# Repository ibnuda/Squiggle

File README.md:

# Squiggle Keyboard

It's a keyboard family which based on my circumstances, preferences, and
observed usages.

Requirements:

- 5 columns per hand.
  My right pinky is almost useless.
- At most 3 keys for each side's thumb row.
  My right thumb key is almost useless.
- No numrow.
  It's harder and more cumbersome to use than a numpad on a layer.
- Split.
  Typing on single flat keyboard hurts my arms in a lot of use cases.
- Symmetric.
  Personal preferences.

This family keyboard repo will not have any of the following features:

- OLED Screen: useless.
- LEDs: useless for me and hurt my eyes.
- Rotary Encoder: useless for me.
- Hotswap: I need a commitment.
- Case for `Low Profile`: defeating the whole purpose of ***LOW*** profile.

## Screenshot

### Standard

- MX and Alps style switches.
- 34 Keys.
- 4x2u thumb keys.
- 2 Promicros.
- TRRS/TRS cable.

### Low Profile

- Dongguan Kaihua Electronics Co., Ltd (originally named Longhua Electronics)'s
  Choc style switches.
- 34 Keys.
- 4x2u thumb keys.
- 2 Promicros.
- TRRS/TRS cable.

### 36 Keys

- MX and Alps style switches.
- 36 Keys.
- 4x2u+2x1.25u thumb keys.
- 2 Promicros.
- TRRS/TRS cable.

### Minimalist

- MX and Alps style switches.
- 34 Keys.
- 4x2u thumb keys.
- 1 Promicros.
- "Amphenol 10 wire" cable.

### Goldberg

(Because it's more complex than necessary. It's just a damn keyboard.)

- MX and Alps style switches.
- 34 - 38 Keys.
- 4x2u or 8x1u thumb keys. (or anything in between)
- 2 Promicros.
- TRRS/TRS cable.

## Confirmed Working PCBs

### Standard

Example firmware: [QMK's master branch](https://github.com/qmk/qmk_firmware/tree/master/keyboards/squiggle/keymaps/rick)

### Goldberg

Example firmware: [QMK's master branch](https://github.com/qmk/qmk_firmware/tree/master/keyboards/squiggle/keymaps/rick-complicated)

### Low Profile

Example firmware: [QMK's master branch](https://github.com/qmk/qmk_firmware/tree/master/keyboards/squiggle/keymaps/rick)

### Minimalist

Example firmware: [Ibnuda's fork](https://github.com/ibnuda/qmk_firmware/tree/squiggle-minimalist/keyboards/squiggle_minimalist/keymaps/rick)

## Disclaimer

I haven't printed some of it. But, theoretically, they should just work.
Oh, if things go wrong, I won't take any responisibilities.

## Additional Note

Any files with `mokou_*.kicad_mod` in `libs/footprints` are made by [Jokan Hiyou](https://twitter.com/jokanhiyou)
and belong to hers.
I just dither them and made them kicad footprints.

## License

GPLv3.

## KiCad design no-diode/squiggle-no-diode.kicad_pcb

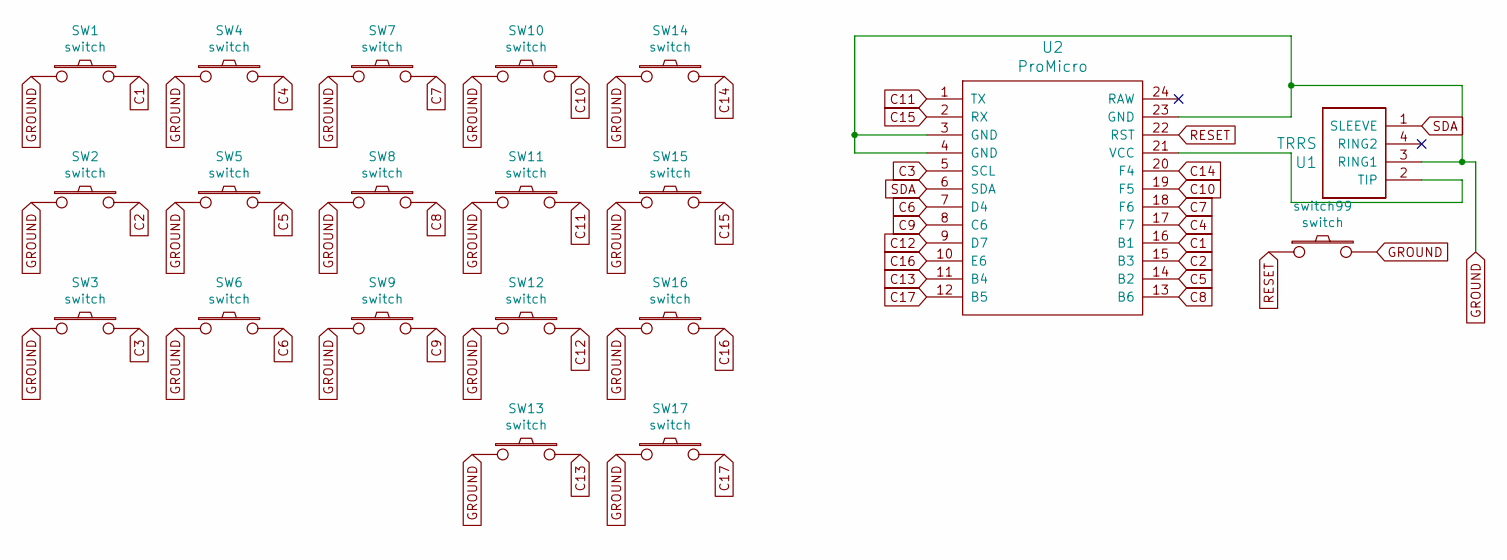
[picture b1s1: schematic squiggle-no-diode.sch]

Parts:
SW1, SW2, SW3, SW4, SW5, SW6, SW7, SW8, SW9, SW10, SW11, SW12, SW14, SW15, SW16: switch; 1u-dual
SW13, SW17: switch; 2u-dual
U1: TRRS; trrs
U2: ProMicro; promicro
switch99: switch; SW_PUSH_6mm_H4.3mm

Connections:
C1: SW1.2, U2.16 (B1)
C2: SW2.2, U2.15 (B3)
C3: SW3.2, U2.5 (SCL)
C4: SW4.2, U2.17 (F7)
C5: SW5.2, U2.14 (B2)
C6: SW6.2, U2.7 (D4)
C7: SW7.2, U2.18 (F6)
C8: SW8.2, U2.13 (B6)
C9: SW9.2, U2.8 (C6)
C10: SW10.2, U2.19 (F5)
C11: SW11.2, U2.1 (TX)
C12: SW12.2, U2.9 (D7)
C13: SW13.2, U2.11 (B4)
C14: SW14.2, U2.20 (F4)
C15: SW15.2, U2.2 (RX)
C16: SW16.2, U2.10 (E6)
C17: SW17.2, U2.12 (B5)
GROUND: SW1.1, SW2.1, SW3.1, SW4.1, SW5.1, SW6.1, SW7.1, SW8.1, SW9.1, SW10.1, SW11.1, SW12.1, SW13.1, SW14.1, SW15.1, SW16.1, SW17.1, U1.3 (RING1), U2.3 (GND), U2.4 (GND), U2.23 (GND), switch99.2
unnamed: U1.2 (TIP), U2.21 (VCC)
RESET: U2.22 (RST), switch99.1
SDA: U1.1 (SLEEVE), U2.6 (SDA)

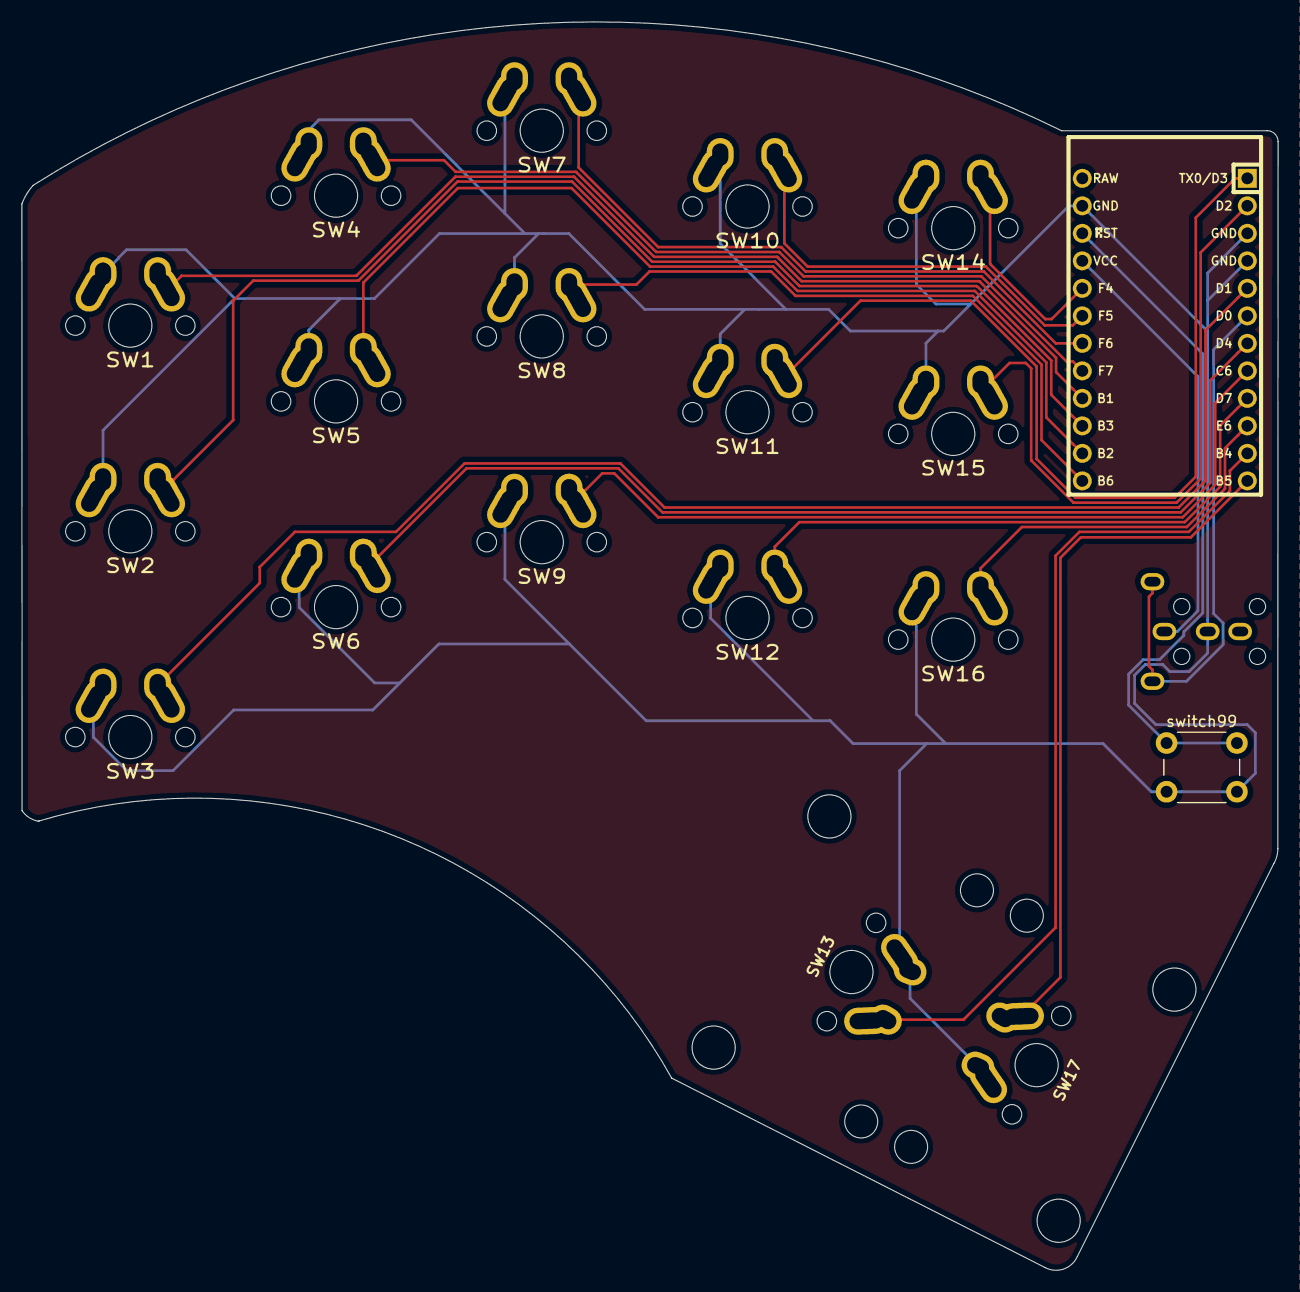
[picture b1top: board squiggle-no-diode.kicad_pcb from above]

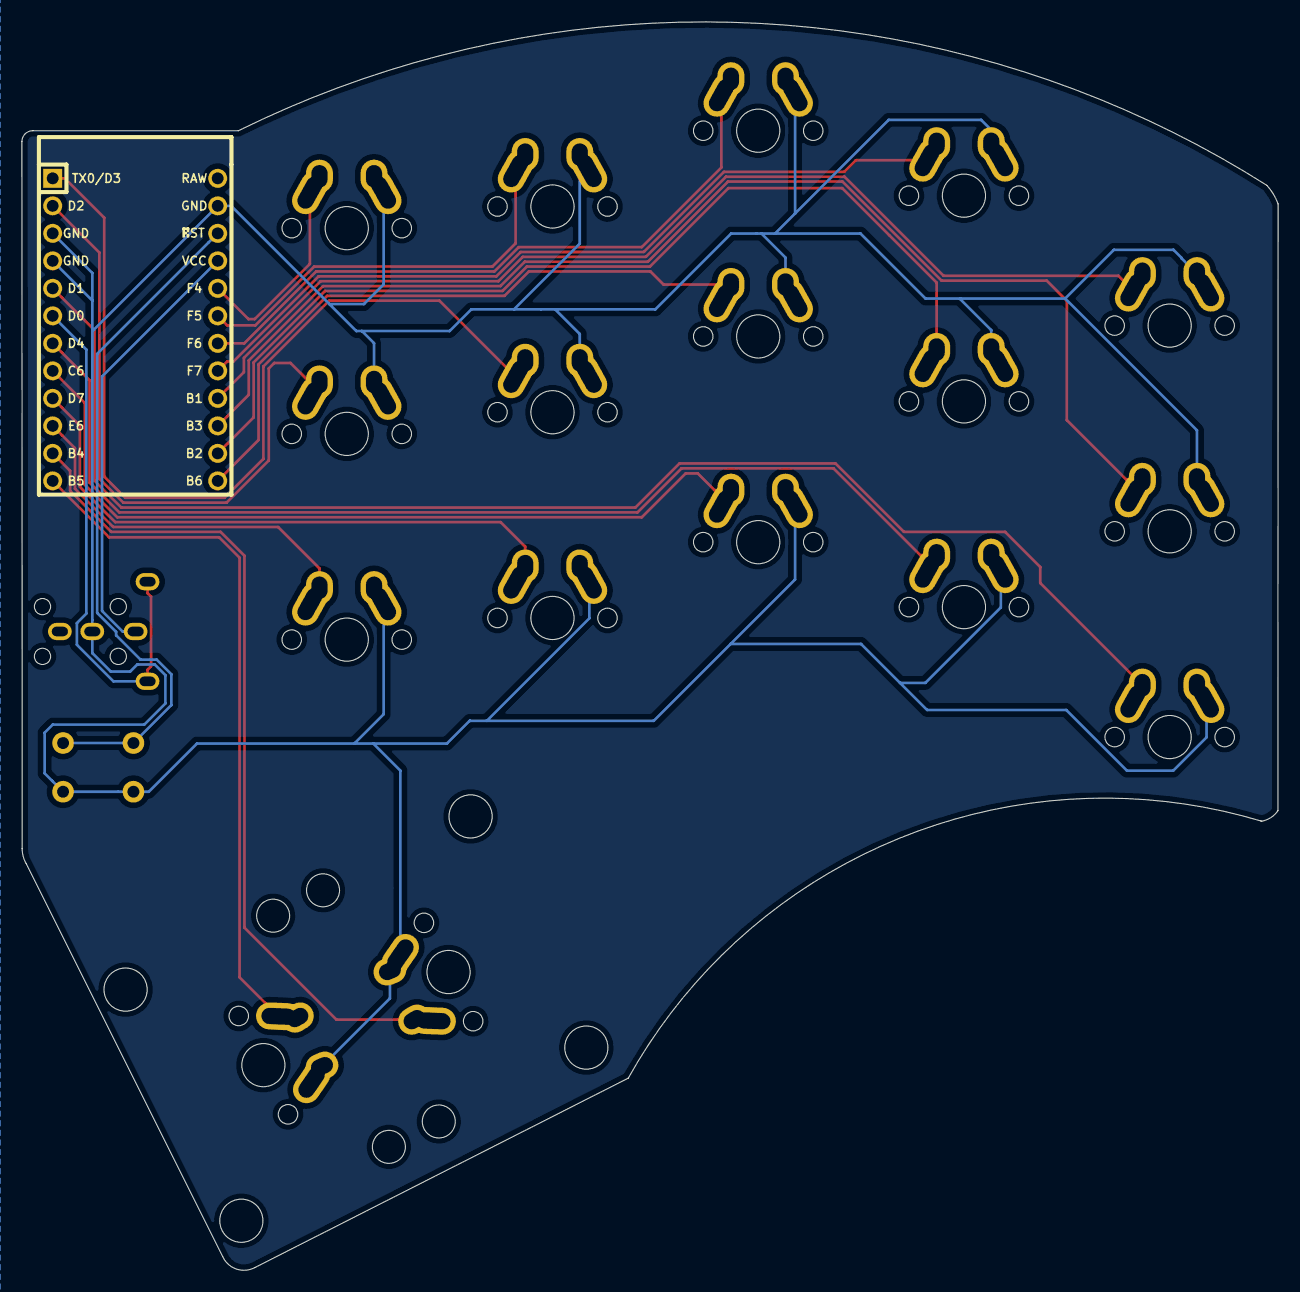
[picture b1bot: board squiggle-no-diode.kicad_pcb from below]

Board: 2 copper layers, 116.0 x 115.3 mm, 20 parts (2 on the bottom side), 21 nets.

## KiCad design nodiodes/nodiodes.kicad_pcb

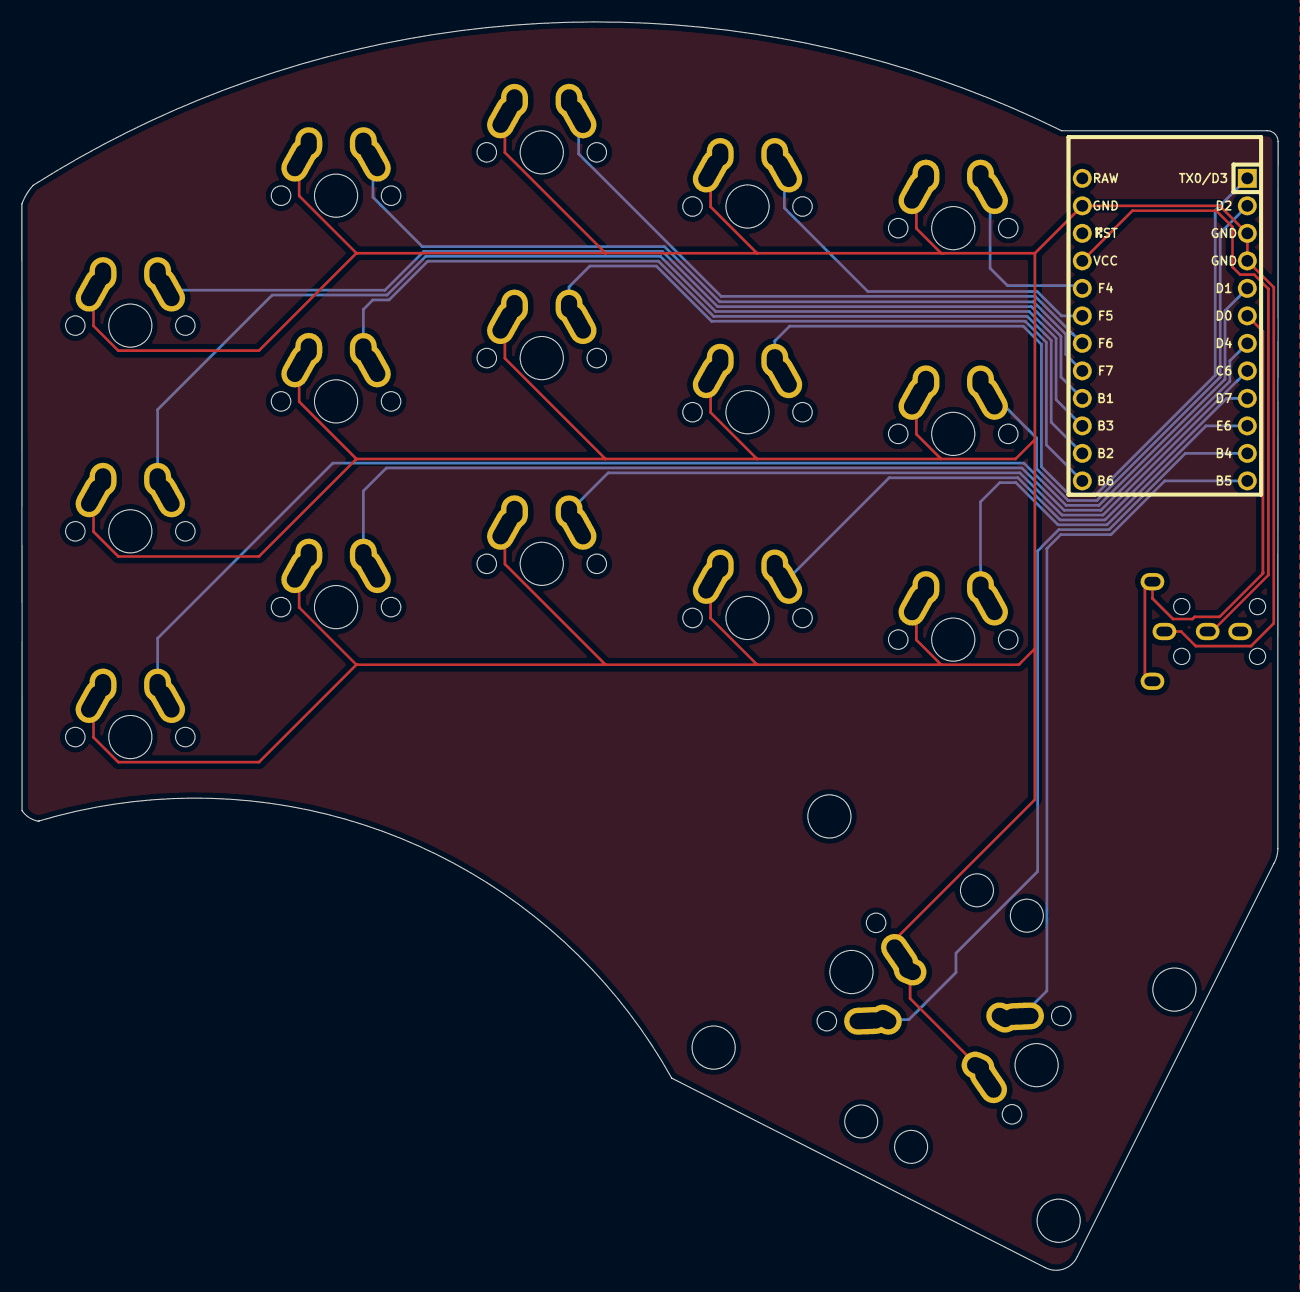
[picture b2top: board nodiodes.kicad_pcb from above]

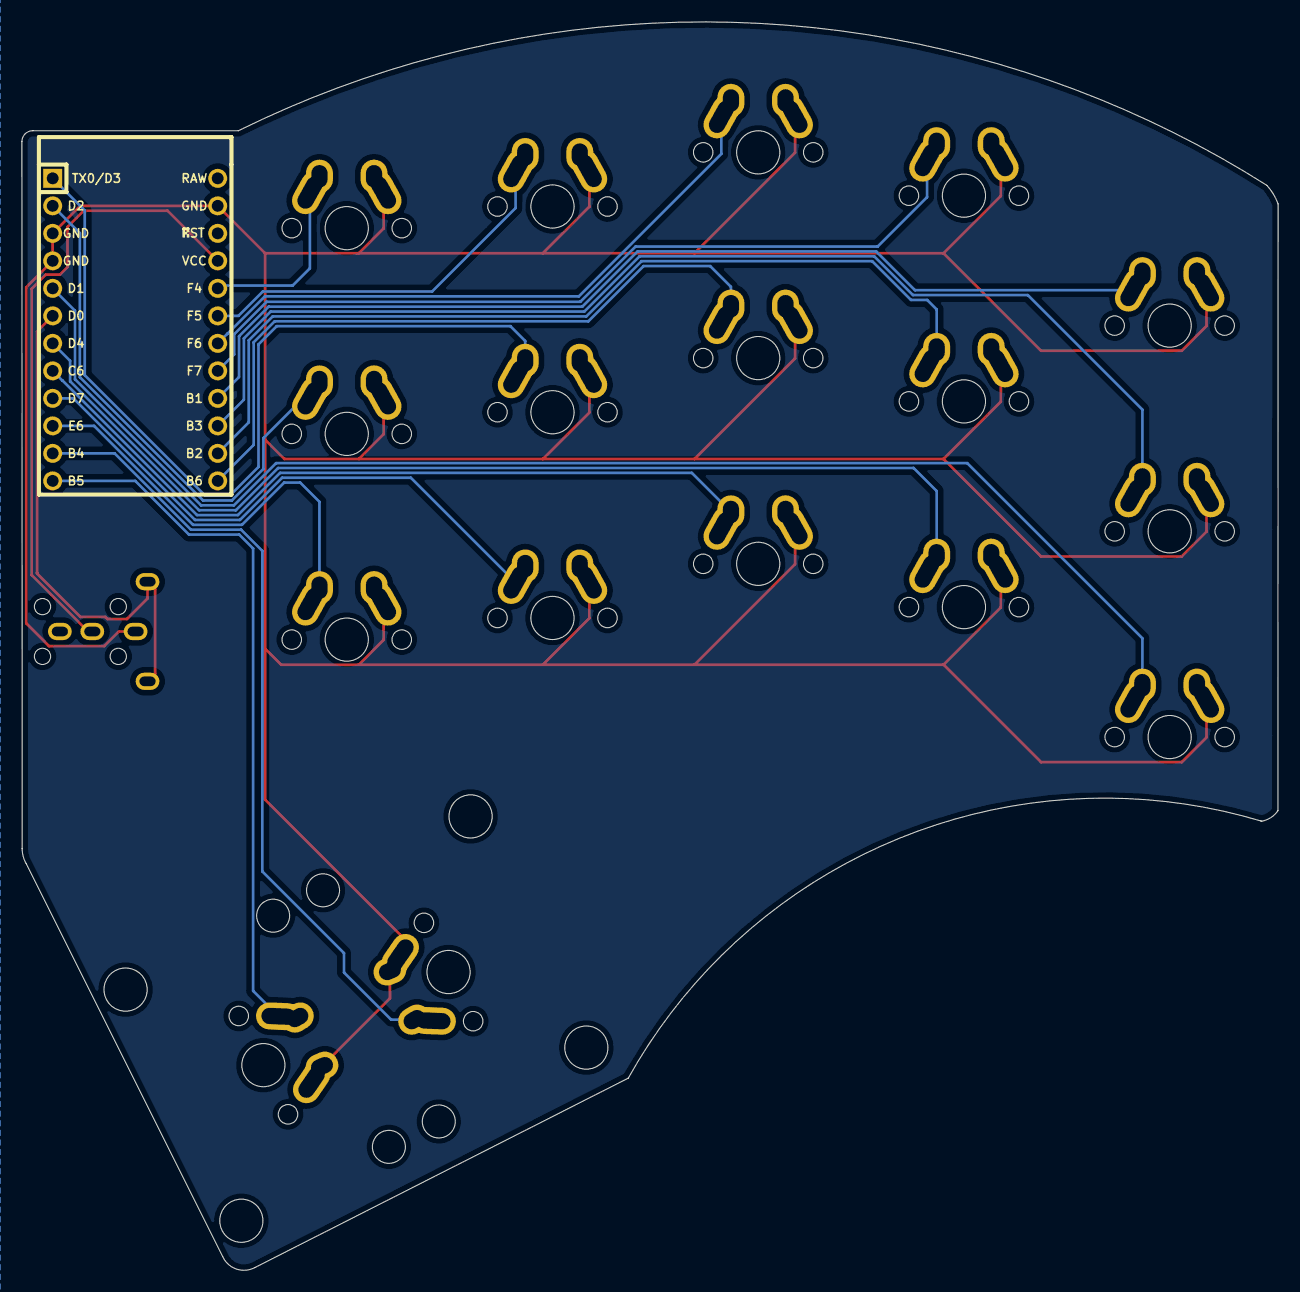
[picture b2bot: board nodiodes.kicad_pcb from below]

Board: 2 copper layers, 116.0 x 115.3 mm, 19 parts (2 on the bottom side), 20 nets.

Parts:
U1: trrs
U2: promicro
switch1, switch2, switch3, switch4, switch5, switch6, switch7, switch8, switch9, switch10, switch11, switch12, switch13, switch14, switch15: switch; 1u-dual
switch16, switch17: switch; 2u-dual

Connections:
GND: U1.2, U2.3, U2.4, U2.23, switch1.1, switch2.1, switch3.1, switch4.1, switch5.1, switch6.1, switch7.1, switch8.1, switch9.1, switch10.1, switch11.1, switch12.1, switch13.1, switch14.1, switch15.1, switch16.1, switch17.1
I11: U2.19, switch4.2
I12: U2.1, switch9.2
I13: U2.9, switch14.2
I21: U2.20, switch5.2
I22: U2.2, switch10.2
I23: U2.10, switch15.2
M1: U2.18, switch3.2
M2: U2.13, switch8.2
M3: U2.8, switch13.2
P1: U2.16, switch1.2
P2: U2.15, switch6.2
P3: U2.5, switch11.2
R1: U2.17, switch2.2
R2: U2.14, switch7.2
R3: U2.7, switch12.2
SDA: U1.1, U2.6
T1: U2.11, switch16.2
T2: U2.12, switch17.2
VCC: U1.3, U2.21

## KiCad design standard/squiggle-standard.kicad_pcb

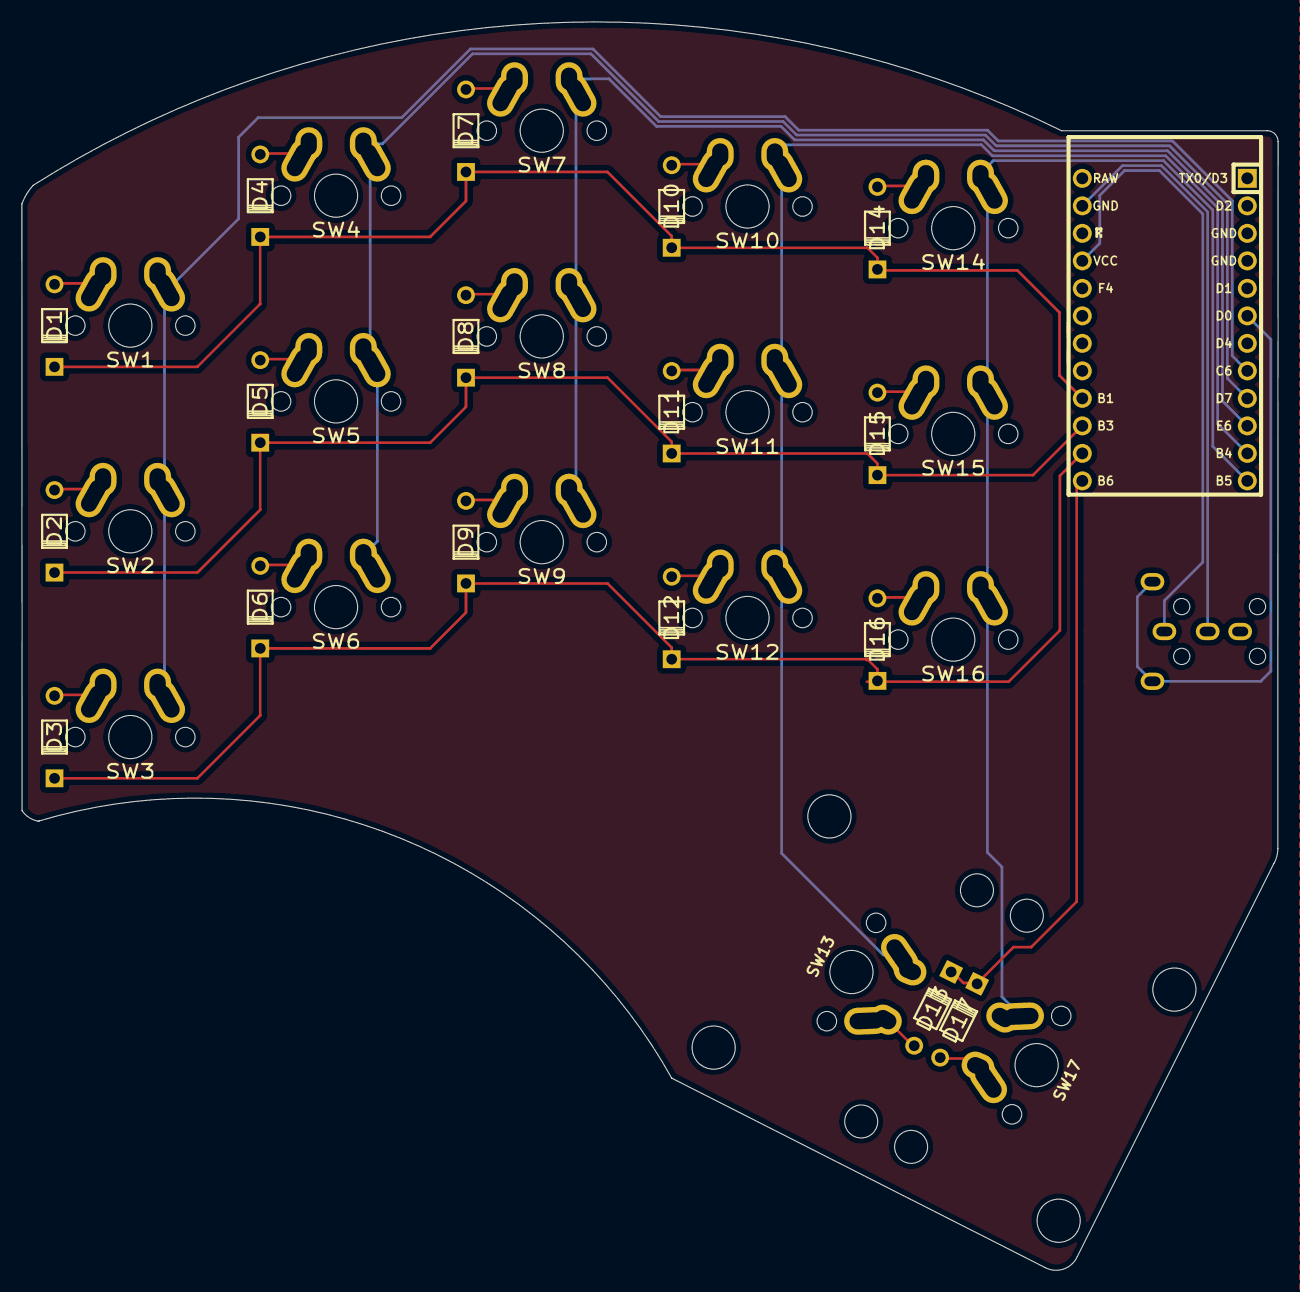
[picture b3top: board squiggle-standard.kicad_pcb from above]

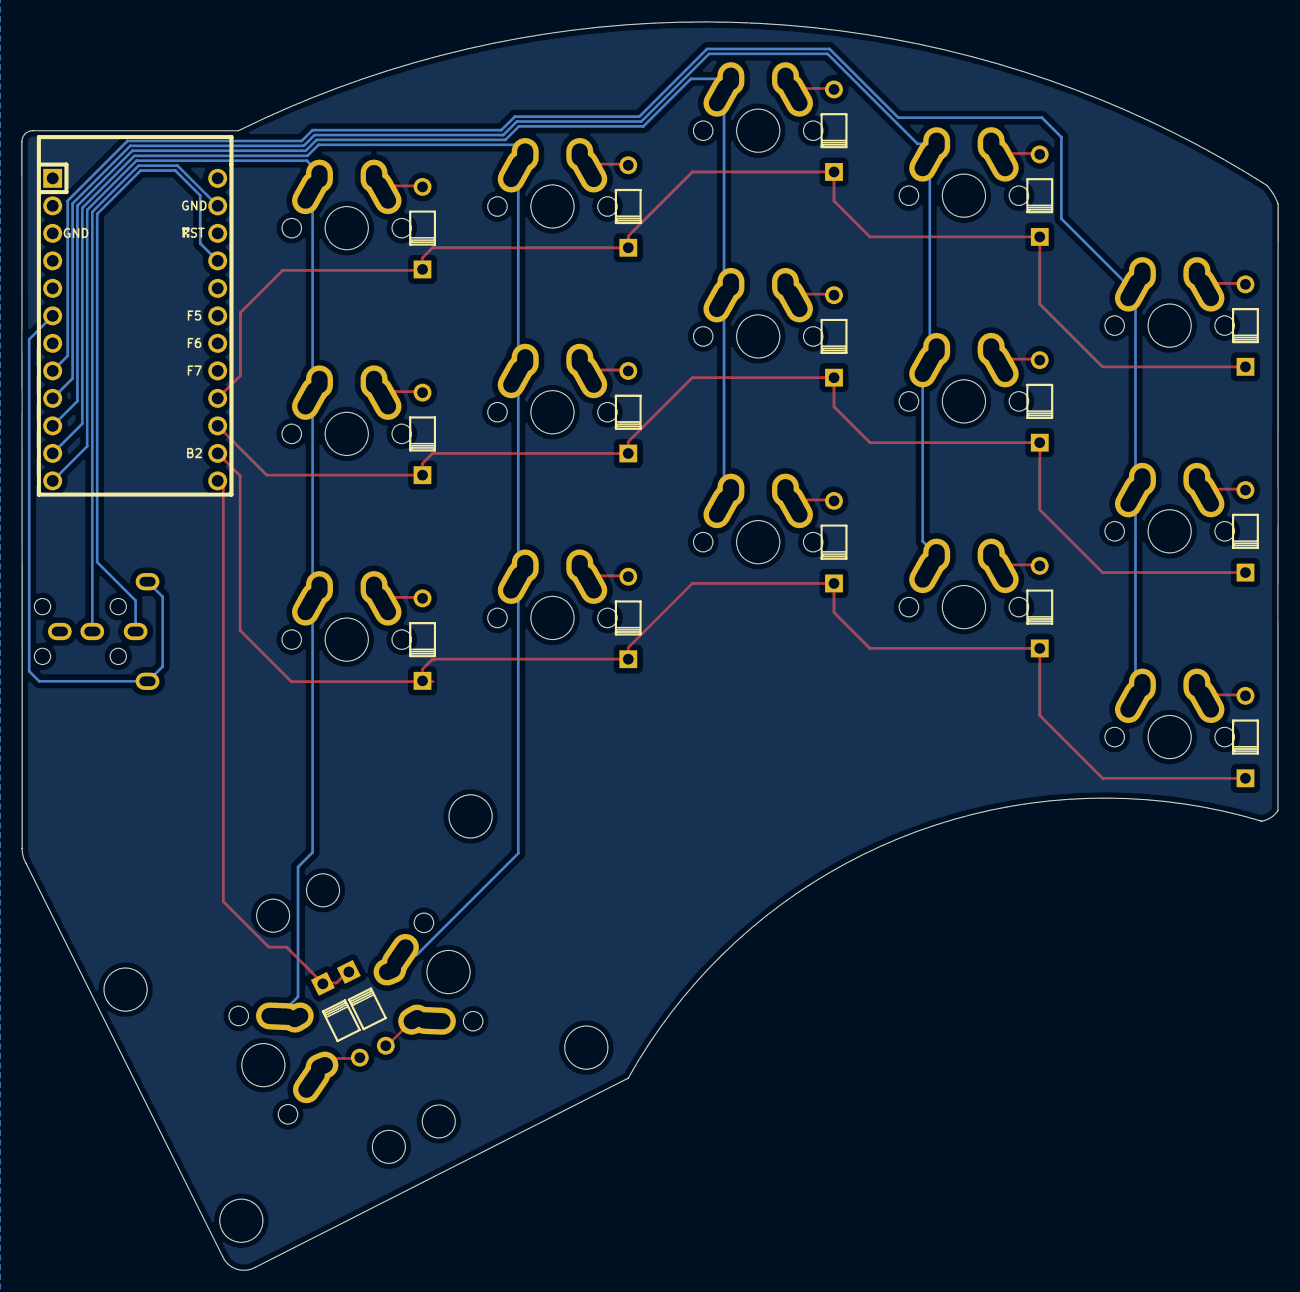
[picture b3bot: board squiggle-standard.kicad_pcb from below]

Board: 2 copper layers, 116.0 x 115.3 mm, 36 parts (2 on the bottom side), 29 nets.

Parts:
D1, D2, D3, D4, D5, D6, D7, D8, D9, D10, D11, D12, D13, D14, D15, D16, D17: D; diode
SW1, SW2, SW3, SW4, SW5, SW6, SW7, SW8, SW9, SW10, SW11, SW12, SW14, SW15, SW16: switch; 1u-dual
SW13, SW17: switch; 2u-dual
U1: TRRS; trrs
U2: ProMicro; promicro

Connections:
COL0: SW1.2, SW2.2, SW3.2, U2.8
COL1: SW4.2, SW5.2, SW6.2, U2.9
COL2: SW7.2, SW8.2, SW9.2, U2.10
COL3: SW10.2, SW11.2, SW12.2, SW13.1, U2.11
COL4: SW14.2, SW15.2, SW16.2, SW17.2, U2.12
unnamed: D1.2, SW1.1
unnamed: D2.2, SW2.1
unnamed: D3.2, SW3.1
unnamed: D4.2, SW4.1
unnamed: D5.2, SW5.1
unnamed: D6.2, SW6.1
unnamed: D7.2, SW7.1
unnamed: D8.2, SW8.1
unnamed: D9.2, SW9.1
unnamed: D10.2, SW10.1
unnamed: D11.2, SW11.1
unnamed: D12.2, SW12.1
unnamed: D13.2, SW13.2
unnamed: D14.2, SW14.1
unnamed: D15.2, SW15.1
unnamed: D16.2, SW16.1
unnamed: D17.2, SW17.1
unnamed: U1.2, U2.21
unnamed: U1.3, U2.23
ROW0: D1.1, D4.1, D7.1, D10.1, D14.1, U2.16
ROW1: D2.1, D5.1, D8.1, D11.1, D15.1, U2.15
ROW2: D3.1, D6.1, D9.1, D12.1, D16.1, U2.14
ROW3: D13.1, D17.1, U2.13
SDA: U1.1, U2.6

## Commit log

2020-04-23 squiggle mx.
2020-04-23 squiggle choc.
2020-04-23 squiggle 36.
2020-04-26 minimalist.
2020-04-26 - added screenshots - added license - added readme
2020-04-27 finished routing minimalist.
2020-04-28 goldberg.
2020-05-17 added stl files for the standard case.
2020-05-27 changed the screw holes' measurement.
2020-06-08 updated readme and added some mokous.
2020-06-16 useless things.
2020-06-17 smoke weed erryday.
2020-06-26 added some things.
    - i really love baldy emojis.
    - another case with nices curves.
2020-06-27 case using minkowsi function.
2020-06-27 softer tenting holder.
2020-07-30 fat-case now have an option to ease model generation.
2020-08-01 added some new footprints.
2020-08-09 finished pics.
2020-09-11 idk lol.
2020-11-26 no diodes
    without any diodes. as requested by @davidphilipbarr
2020-11-29 added support for minimalist.
2020-12-04 i forgot what i did.
